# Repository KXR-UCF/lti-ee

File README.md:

# lti-ee
Electrical Documentation for LTI electronics projects

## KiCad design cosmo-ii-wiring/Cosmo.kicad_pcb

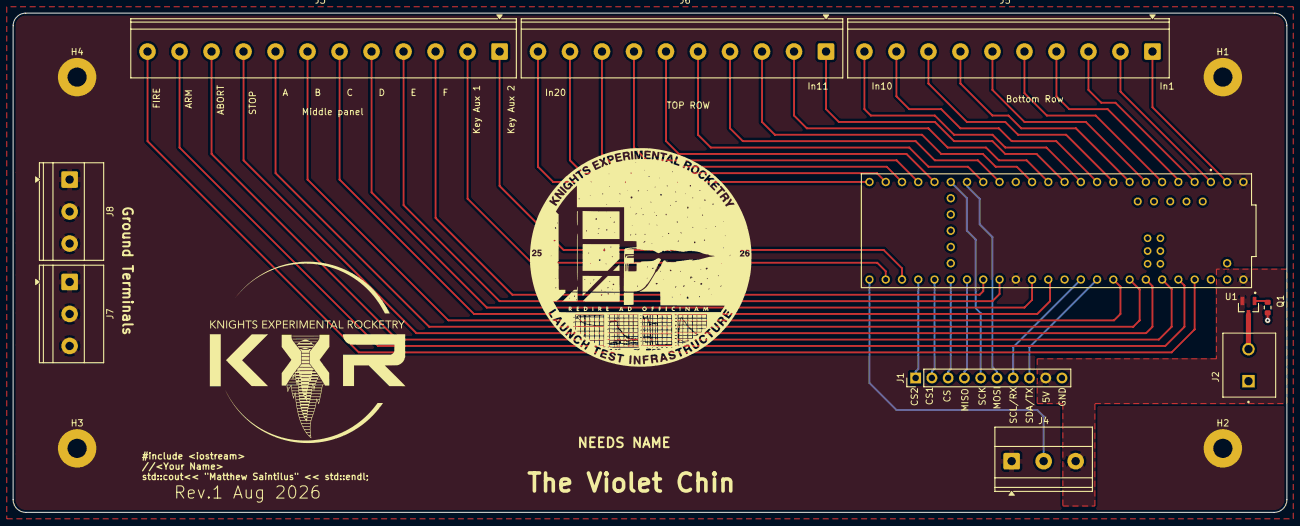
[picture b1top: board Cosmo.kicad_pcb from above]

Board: 2 copper layers, 199.0 x 78.0 mm, 15 parts (0 on the bottom side), 45 nets.

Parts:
H1, H2, H3, H4: MountingHole_Pad; MountingHole_3mm_Pad
J1: Conn_01x10; PinHeader_1x10_P2.54mm_Vertical
J2: 3.5mm; PHOENIX_1935161
J3: Screw_Terminal_01x12; TerminalBlock_Phoenix_PT-1,5-12-5.0-H_1x12_P5.00mm_Horizont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
J4, J7, J8: Screw_Terminal_01x03; TerminalBlock_Phoenix_MKDS-1,5-3_1x03_P5.00mm_Horizontal
J5, J6: Screw_Terminal_01x10; TerminalBlock_Phoenix_PT-1,5-10-5.0-H_1x10_P5.00mm_Horizont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
Q1: IRLML5103TRPBF; SOT95P237X112-3N
R1: 10k; R_0603_1608Metric
U1: Teensy4.1; Teensy4.1Footy

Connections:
/5V: J1.9, J4.3, Q1.2 (S), U1.VIN
/5V_Raw: J2.2, Q1.3 (D)
/A: J3.8, U1.19 (18)
/ARM: J3.11, U1.22 (22_A8_CTX1)
/Abort: J3.10, U1.21 (21_A7_RX5_BCLK1)
/B: J3.7, U1.18 (18_A4_SDA)
/C: J3.6, U1.14 (14_A0_TX3_SPDIF_OUT)
/CS: J1.3, U1.38 (38_CS1_IN1)
/CS1: J1.2, U1.37 (37_CS)
/CS2: J1.1, U1.36 (36_CS)
/D: J3.5, U1.13 (13_SCK_LED)
/E: J3.4, U1.41 (41_A17)
/F: J3.3, U1.40 (40_A16)
/Fire: J3.12, U1.23 (23_A9_CRX1_MCLK1)
/In1: J5.1, U1.0 (0_RX1_CRX2_CS1)
/In2: J5.2, U1.1 (1_TX1_CTX2_MISO1)
/In3: J5.3, U1.2 (2_OUT2)
/In4: J5.4, U1.3 (3_LRCLK2)
/In5: J5.5, U1.4 (4_BCLK2)
/In6: J5.6, U1.5 (5_IN2)
/In7: J5.7, U1.6 (6_OUT1D)
/In8: J5.8, U1.7 (7_RX2_OUT1A)
/In9: J5.9, U1.8 (8_TX2_IN1)
/In10: J5.10, U1.9 (9_OUT1C)
/In11: J6.1, U1.10 (10_CS_MQSR)
/In12: J6.2, U1.11 (11_MOSI_CTX1)
/In13: J6.3, U1.12 (12_MISO_MQSL)
/In14: J6.4, U1.24 (24_A10_TX6_SCL2)
/In15: J6.5, U1.25 (25_A11_RX6_SDA2)
/In16: J6.6, U1.28 (28_RX7)
/In17: J6.7, U1.29 (29_TX7)
/In18: J6.8, U1.30 (30_CRX3)
/In19: J6.9, U1.31 (31_CTX3)
/In20: J6.10, U1.32 (32_OUT1B)
/Key Aux 1: J3.2, U1.34 (34_RX8)
/Key Aux 2: J3.1, U1.35 (35_TX8)
/LED: J4.2, U1.33 (33_MCLK2)
/MISO: J1.4, U1.39 (39_MISO1_OUT1A)
/MOSI: J1.6, U1.26 (26_A12_MOSI1)
/SCK: J1.5, U1.27 (27_A13_SCK1)
/SCL/RX: J1.7, U1.16 (16_A2_RX4_SCL1)
/SDA/TX: J1.8, U1.17 (17_A3_TX4_SDA1)
/Stop: J3.9, U1.20 (20_A6_TX5_LRCLK1)
GND: H1.1 (1_1), H2.1 (1_1), H3.1 (1_1), H4.1 (1_1), J1.10, J2.1, J4.1, J7.1, J7.2, J7.3, J8.1, J8.2, J8.3, R1.1, U1.GND1 (GND), U1.GND2 (GND), U1.GND3 (GND)
unnamed: Q1.1 (G), R1.2
